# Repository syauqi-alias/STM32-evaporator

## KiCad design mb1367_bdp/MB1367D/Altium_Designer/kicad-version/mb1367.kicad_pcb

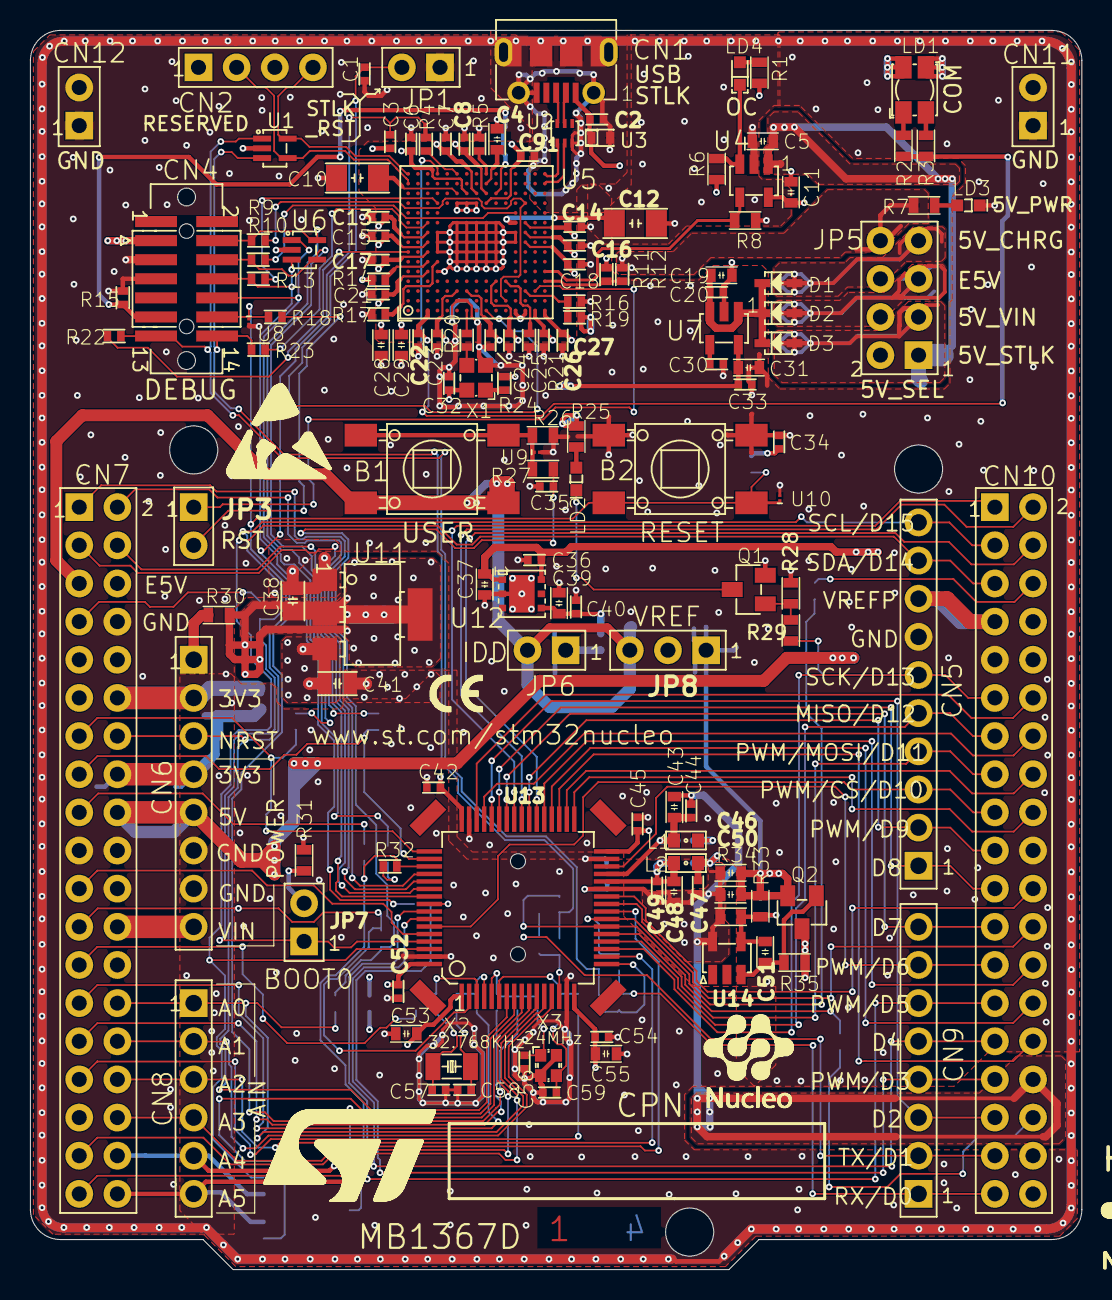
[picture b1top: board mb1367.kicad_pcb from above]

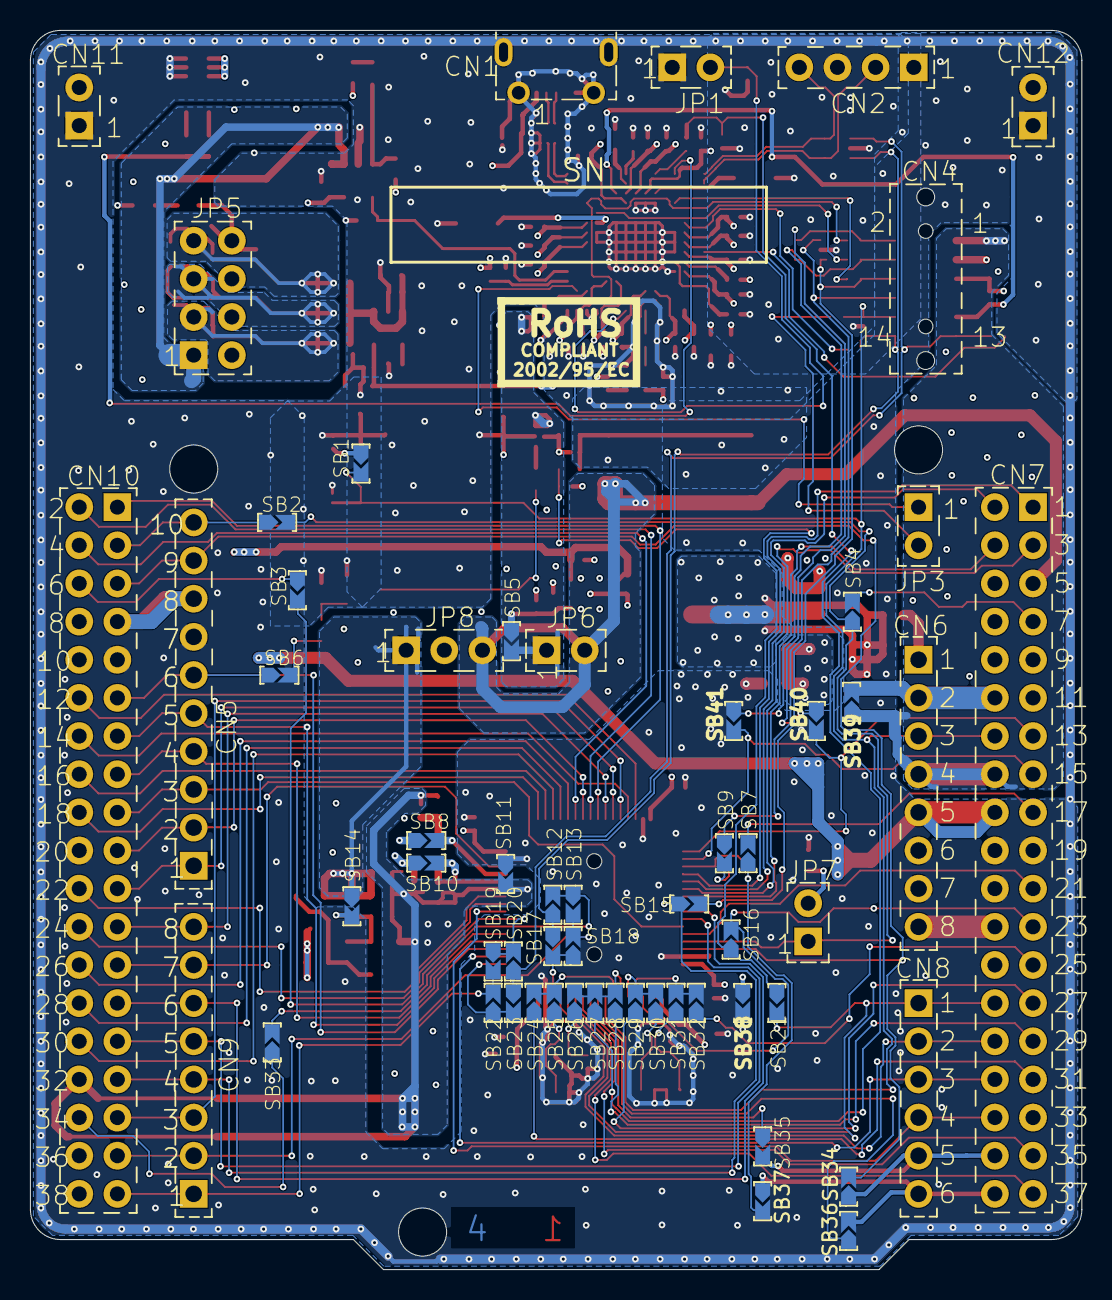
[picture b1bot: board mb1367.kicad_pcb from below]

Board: 4 copper layers, 70.0 x 82.5 mm, 187 parts (41 on the bottom side), 143 nets.

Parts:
B1: SWI_WEALTHMETAL_TD-0341_4P_BLUE
B2: SWI_WEALTHMETAL_TD-0341_4P_BLACK
C1, C6, C7, C8, C9, C13, C14, C15, C16, C17, C18, C20, C21, C22, C23, C24, C25, C26, C27, C32, C33, C34, C35, C36, C40, C42, C44, C45, C47, C49, C52, C54: Capacitor; C0402
C2, C3, C30, C56, C57, C58, C59: C0402
C4, C5, C11, C19, C28, C29, C31, C37, C39, C43, C46, C48, C50, C51, C53, C55: C0603
C10, C12: C1206_H1P15
C38, C41: C0805
CN1: CON_USBMICROB_MOLEX_105017-0001_H2P90
CN2: CON_SAMTEC_TSW-104-07-G-S
CN4: CON_STDC14_Receiver_MEDIUM_WITH_MIPI10_3D
CN5: CON_SAMTEC_SSW-110-03-X-S
CN6, CN9: CON_SAMTEC_SSW-108-03-X-S
CN7, CN10: CON_SAMTEC_TSW-119-09-X-D
CN8: CON_SAMTEC_SSW-106-03-X-S
CN11, CN12: CON_SAMTEC_TSW-102-09-X-S
D1, D2, D3: DIO_SOD323
HW103: LOGO_NUCLEO
HW104: LOGO_CE
HW105: LOGO_ROHS
HW106: LOGO_ST
HW107: LOGO_MAIN_1
JP1, JP7: CON_SAMTEC_TSW-102-07-G-S
JP3, JP6: Shunt Fitted; CON_SAMTEC_TSW-102-07-G-S
JP5: CON_SAMTEC_TSW-104-07-X-D
JP8: CON_SAMTEC_TSW-103-07-F-S
L1, L2: L0603
LD1: LD_BICOLOR_CMS; LED_BI-GR_HSMF-A201-A00J1
LD2, LD3: LED_green; LED_0603_GREEN
LD4: LED_red; LED_0603_VISHAY_VLMS1300-GS08_RED_1A2K_H0P8
Q1, Q2: NPN_SOT23
R1, R6, R7, R8, R25, R26, R27, R28, R29, R30, R31, R33, R34, R35: R0603
R2, R3: Resistor; R0603
R4, R15, R20: Resistor; R0402
R5, R9, R10, R11, R12, R13, R14, R16, R17, R18, R19, R21, R22, R23, R24, R32: R0402
SB1, SB2, SB3, SB4, SB5, SB6, SB7, SB8, SB9, SB10, SB11, SB12, SB13, SB14, SB15, SB16, SB17, SB18, SB19, SB20, SB21, SB22, SB23, SB24, SB25, SB26, SB27, SB28, SB29, SB30, SB31, SB32, SB33, SB34, SB35, SB36, SB37, SB38, SB39, SB40, SB41: SOLDER-BRIDGE_R0603-0R
U1, U6: ESD_SOT323-5L
U2: ​; ESD_QFN-6L_1P7X1P5_P050
U3: ESD_QFN2_1P6X1_P125
U4: MOS_SOT23-5L
U5: ICC_UFBGA201_176+25_10X10_P065
U7: REG_SOT23-5L
U8, U9, U10: ESD-TRANSIL; ESD_0201_H0P3_1K_2A
U11: REG_SOT223-TAB
U12: ICC_DFN6-EPAD_3X3_P095
U13: ICC_LQFP64_10X10_P050_SOCKET_YAMAICHI_IC149-064-069-B5_NM
U14: ICC_SOT23-5L_H1P45
X1: OSC_NDK_NZ2520SB_4P
X2: CRY_NX3215SA_2P
X3: CRY_NX2016SA_4P

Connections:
3V3: CN4.3, CN6.4, CN7.16, JP6.1, R19.2, R25.1, SB5.2, SB39.1
3V3_STLK: C6.2, C7.2, C8.2, C9.2, C13.2, C14.2, C15.2, C16.2, C17.2, C18.2, C21.2, C22.2, C23.2, C24.2, C25.2, C26.2, C27.2, C28.2, C29.2, C31.2, C32.2, C33.2, CN2.1, LD1.4, R14.1, R24.1, U5.C1, U5.C5, U5.C7, U5.C8, U5.C9, U5.F3, U5.G3, U5.G13, U5.H13, U5.J12, U5.J13, U5.K4, U5.N8, U5.N9, U5.N10, U5.P1, U5.R1, U7.5, X1.4
5V: C36.2, C37.2, CN6.5, CN7.18, JP5.2, JP5.4, JP5.6, JP5.8, Q2.3, R7.2, R12.1, R35.2, U12.1, U12.6
5V_USB_CHGR: C2.2, C11.2, CN1.1, CN10.8, D1.1, JP5.7, R1.2, R6.2, U3.1, U4.5
5V_USB_STLK: C5.2, JP5.1, U4.1
5V_VIN: C38.2, D3.1, JP5.3, R30.2, U11.2, U11.4
AGND: C43.1, C44.1, C46.1, C47.1, C48.2, C49.2, C50.1, CN10.32, R34.1, SB11.2, U13.27, U14.5
ARD_D0_RX: CN9.1, CN10.37, SB19.2, SB22.2
ARD_D1_TX: CN9.2, CN10.35, SB13.2, SB18.2
AVDD: C43.2, C44.2, L1.2, SB8.2, U13.29
B_USER: C35.2, R27.2, SB16.1, SB21.1
E5V: CN7.6, D2.1, JP5.5
GND: B2.3, B2.4, C1.1, C2.1, C3.1, C4.1, C5.1, C6.1, C7.1, C8.1, C9.1, C10.1, C11.1, C12.1, C13.1, C14.1, C15.1, C16.1, C17.1, C18.1, C19.1, C20.1, C21.1, C22.1, C23.1, C24.1, C25.1, C26.1, C27.1, C28.1, C29.1, C30.1, C31.1, C32.1, C33.1, C34.1, C35.1, C36.1, C37.1, C38.1, C39.1, C40.1, C41.1, C42.1, C45.1, C52.1, C53.1, C54.1, C55.1, C56.1, C57.2, C58.2, C59.1, CN1.5, CN1.6, CN1.7, CN1.8, CN1.9, CN1.10, CN1.11, CN2.3, CN4.5, CN4.7, CN5.7, CN6.6, CN6.7, CN7.8, CN7.19, CN7.20, CN7.22, CN10.9, CN10.20, CN11.1, CN11.2, CN12.1, CN12.2, JP1.1, LD1.1, LD3.2, Q1.2, R5.1, R8.2, R11.1, R15.1, R16.2, R17.1, R21.1, R26.1, R28.1, R31.1, SB11.1, U1.2, U2.3, U3.2, U4.2, U5.D5, U5.D7, U5.D8, U5.D9, U5.F2, U5.F6, U5.F7, U5.F8, U5.F9, U5.F10, U5.F12, U5.G2, U5.G6, U5.G7, U5.G8, U5.G9, U5.G10, U5.G12, U5.H6, U5.H7, U5.H8, U5.H9, U5.H10, U5.H12, U5.J6, U5.J7, U5.J8, U5.J9, U5.J10, U5.K6, U5.K7, U5.K8, U5.K9, U5.K10, U5.M1, U5.M8, U5.M9, U5.N1, U6.2, U7.2, U8.2, U9.2, U10.2, U11.1, U12.2, U12.EP, U13.15, U13.31, U13.47, U13.63, X1.2, X3.2, X3.4
GNDDetect: CN4.11, R15.2, U5.K13
IOREF: CN6.2, CN7.12, SB39.2
LED_STLK: R2.2, R3.2, U5.D15
MCO: C3.2, R4.2, SB27.1
NetB1_3: B1.3, B1.4, R26.2, R27.1, U9.1
NetC1_2: C1.2, JP1.2, U5.J1
NetC4_2: C4.2, U5.J14
NetC10_2: C10.2, U5.F13
NetC12_2: C12.2, U5.M10
NetC19_2: C19.2, C20.2, D1.2, D2.2, D3.2, U7.1, U7.3
NetC30_2: C30.2, U7.4
NetC34_2: C34.2, SB1.1
NetC39_2: C39.2, C40.2, SB5.1, U12.4
NetC47_2: C47.2, JP8.2, L2.1, SB10.1
NetC51_1: C51.1, Q2.1, R35.1, U14.3
NetC51_2: C51.2, R33.1, R34.2, SB14.2, U14.4
NetCN5_10: CN5.10, CN10.3, SB2.1
NetCN6_1: CN6.1, R30.1
NetCN7_7: CN7.7, SB4.2
NetCN7_17: CN7.17, SB7.2
NetCN7_36: CN7.36, CN8.5, SB34.1, SB35.2
NetCN7_38: CN7.38, CN8.6, SB36.2, SB37.1
NetCN10_6: CN10.6, SB3.1
NetCN10_34: CN10.34, SB33.1
NetJP3_2: JP3.2, R18.1
NetJP7_2: JP7.2, R31.2
NetLD1_2: LD1.2, R3.1
NetLD1_3: LD1.3, R2.1
NetLD2_1: LD2.1, R25.2
NetLD2_2: LD2.2, Q1.3
NetLD3_1: LD3.1, R7.1
NetLD4_1: LD4.1, R1.1
NetLD4_2: LD4.2, R6.1, U4.3
NetQ1_1: Q1.1, R28.2, R29.2
NetR4_1: R4.1, U5.F15
NetR5_2: R5.2, U5.J15
NetR14_2: R14.2, U5.C6
NetR16_1: R16.1, R19.1, U5.N3
NetR17_2: R17.2, U5.D6
NetR20_1: R20.1, X1.3
NetR20_2: R20.2, U5.G1
NetR21_2: R21.2, U5.L4
NetR24_2: R24.2, X1.1
NetR29_1: R29.1, SB6.2
NetR32_1: R32.1, SB9.2
NetSB24_2: SB24.2, SB25.2, U13.6
NetSB26_2: SB26.2, SB27.2, SB28.2, U13.5
NetSB29_2: SB29.2, SB30.2, U13.4
NetSB31_2: SB31.2, SB32.2, U13.3
OSC32_IN: C57.1, SB31.1, X2.1
OSC32_OUT: C58.1, SB30.1, X2.2
OSC_IN: C56.2, SB26.1, X3.1
OSC_OUT: C59.2, SB25.1, X3.3
PA0: CN7.28, CN8.1, SB21.2, U13.12
PA1: CN7.30, CN8.2, U13.13
PA2: SB17.2, SB18.1, U13.14
PA3: SB22.1, SB23.2, U13.17
PA4: CN7.32, CN8.3, U13.18
PA5: CN5.6, CN10.11, SB6.1, U13.19
PA6: CN5.5, CN10.13, U13.20
PA7: CN5.4, CN10.15, U13.21
PA8: CN9.8, CN10.23, U13.42
PA9: CN5.1, CN10.21, U13.43
PA10: CN9.3, CN10.33, U13.44
PA11: CN10.14, U13.45
PA12: CN10.12, U13.46
PA13: CN7.13, SB40.2, U13.49
PA14: CN7.15, SB41.2, U13.50
PA15: R32.2, SB7.1, SB37.2, U13.51
PB0: CN7.34, CN8.4, U13.24
PB1: CN10.24, U13.25
PB2: CN10.22, U13.26
PB3: CN9.4, CN10.31, SB15.1, U13.56
PB4: CN9.6, CN10.27, U13.57
PB5: CN9.5, CN10.29, U13.58
PB6: CN5.3, CN10.17, U13.59
PB7: CN7.21, U13.60
PB8: JP7.1, SB2.2, SB4.1, U13.61
PB9: CN5.9, CN10.5, SB34.2, U13.62
PB10: CN9.7, CN10.25, U13.30
PB11: CN10.18, U13.33
PB12: CN10.16, U13.34
PB13: CN10.30, U13.35
PB14: CN10.28, U13.36
PB15: CN10.26, U13.37
PC0: SB36.1, U13.8
PC1: SB35.1, U13.9
PC2: CN7.35, U13.10
PC3: CN7.37, U13.11
PC4: SB12.2, SB13.1, SB33.2, U13.22
PC5: SB3.2, SB19.1, SB20.2, U13.23
PC6: CN10.4, U13.38
PC7: CN5.2, CN10.19, U13.39
PC8: CN10.2, U13.40
PC9: CN10.1, U13.41
PC10: CN7.1, U13.52
PC11: CN7.2, U13.53
PC12: CN7.3, U13.54
PC13: CN7.23, SB16.2, U13.2
PC14: CN7.25, SB32.1
PC15: CN7.27, SB29.1
PD2: CN7.4, U13.55
PF0: CN7.29, SB28.1
PF1: CN7.31, SB24.1
STLK_SWCLK: CN2.2, U1.4, U5.A14
STLK_SWDIO: CN2.4, U1.5, U5.A15
STLK_VCP_RX: R23.1, U5.C10
STLK_VCP_TX: R22.1, U5.A7
T_JTDI: CN4.10, SB9.1, U6.1
T_NRST: B2.1, B2.2, CN4.12, CN6.3, CN7.14, R18.2, SB1.2, U8.1, U10.1, U13.7
T_NRSTa: JP3.1, U5.P3
T_PWR_EN: R8.1, U4.4, U5.R5
T_PWR_EXT: R11.2, R12.2, U5.R4
T_SWCLK: CN4.6, R10.2, SB41.1, U6.4
T_SWCLKa: R10.1, U5.M11
T_SWDIO: CN4.4, R9.2, SB40.1, U6.5
T_SWDIOa: R9.1, U5.L2, U5.N12
T_SWO: CN4.8, R13.2, SB15.2, U6.3
T_SWOa: R13.1, U5.D12
T_VCP_RX: CN4.13, R22.2, SB20.1, SB23.1, U1.1
T_VCP_TX: CN4.14, R23.2, SB12.1, SB17.1, U1.3
USB_DEV_HS_CN_N: CN1.2, U2.5
USB_DEV_HS_CN_P: CN1.3, U2.6
USB_DEV_HS_N: U2.2, U5.R14
USB_DEV_HS_P: U2.1, U5.R15
VBAT: C53.2, CN7.33, SB38.2, U13.1
VDD: B1.1, B1.2, C42.2, C45.2, C52.2, C54.2, C55.2, CN7.5, JP6.2, JP8.3, L1.1, SB8.1, SB38.1, U13.16, U13.32, U13.48, U13.64
VIN: C41.2, CN6.8, CN7.24, U11.3
VREF: C46.2, C50.2, JP8.1, Q2.2, R33.2, SB14.1
VREFP: C48.1, C49.1, CN5.8, CN10.7, L2.2, SB10.2, U13.28
